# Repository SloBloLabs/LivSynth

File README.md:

# Youtube

Watch the related [Demo Video] on Youtube for a workout in musical context.

Watch the corresponding [Video Manual] on Youtube for a detailed feature explanation.

[Demo Video]: https://youtu.be/7tzhh7atj4o
[Video Manual]: https://youtu.be/lYTFUqn5oQk

# Build Instructions

How to convert a CubeMX / CubeIDE project to GNU ARM Toolchain with CMake, openocd and VS Code

Prerequisites

Available on PATH
 - ARM toolchain
 - make
 - cmake
 - openocd

VS Code extensions
 - MS C/C++
 - MS C/C++ Extension Pack
 - Cortex Debug

---

Workflow

Copy to project directory:
 - README.md
 - Makefile
 - CMakeLists.txt
 - cmake folder with arm toolchain cmake directives
 - .gitignore file
 - swvtrace.sh
 - svd file (optional)
 - folder .vscode/launch.json and adapt settings
 - folder "App"

then
 - Adapt settings in CMakeLists.txt header
 - rename myAppMain [.hpp/.cpp]
 - include myAppMain.hpp in Core/Src/main.c
 - add projectMain() to main.c (right before while loop)
 - right click CMakeLists.txt -> configure all projects
 - start coding

Tested on
 - Mac
 - Linux

2022-03-08: There is an issue using ARM Toolchain 11.2.1: https://community.arm.com/support-forums/f/compilers-and-libraries-forum/52377/internal-compiler-errors-with-arm-none-eabi-gcc-11-2-2022-02-on-macs-with-apple-silicon
Stick with 10.3 for now!!
2022-11-13: The issue is solved within Toolchain version 11.3.1

---

Upload to github
 - git init
 - git add .
 - git config user.name "<<username>>"
 - git config user.email "<<email>>"
 - git commit -m "First commit"
 - git branch -M main
 - git remote add origin https://github.com/SloBloLabs/<"ProjectRepo">.git
 - git push -u origin main

--

Update github access token
 - git remote remove origin
 - git remote add origin https://oauth2:<<new oauth token>>@github.com/<<username>>/<<reponame>>.git
 - git remote -v

--

Bake a new release on Github:
git tag <tagname> // e.g. v0.2.1
git push origin <tagname>

--
# STM32 USB Composite device

Composite USB interface:

1 configuration
3 interfaces (2*CDC + 1*MIDI)
6 endpoints

CDC:
 - 2 interfaces
   - 0: communications control
     - 1 endpoint 0x82
   - 1: communications data
     - 2 endpoints 0x01 + 0x81 (BULK)
 - 4 endpoints overall
   - EP0
   - EP1
   - EP3 (in only: 0x83)

MIDI:
 - 1 interface
   - 0: Audio/Streaming
     - 2 endpoints 0x02 + 0x83 (BULK)
 - 3 endpoints overall
   - EP0
   - EP2

# Build Instructions

Use the ibom tool inside the hardware section of the repository to track your work!
## Power
 - Place USB Micro Connector J21
 - Place all components from power section
   - U8
   - D12
   - FB1
   - U1
   - J24, J24, J12, J7
   - C49, C52, C32, C33, C1, C2, C3, C7
   - R1, R2, R11
   - SW7
 - Check voltages at J201, do proceed if everything is ok!

## Assembly of backside
 - assemble all components (except 5mm LEDs!) on the backside of the mainboard, preferably using the following order:
   - SMD components
   - resistors
   - diodes
   - DIP socket and DIP components
   - transistors (Q4/Q5, Q8/Q9 and Q11/Q12 must be matched)
   - tempco resistor
   - pin headers
   - capacitors

## Assemply of frontside
 - assemble potentiometers, trimmers, spacers and switches of the mainboard, DO NOT SOLDER THEM YET!
 - put the faceplate on top and make sure all components incl. trimmers fit into the wholes
 - fasten the M2.5 screws in the corners
 - turn the set around and solder everthing
 - remove the faceplate again

## Assmebly of speaker
 - First put screws from backside, hex nuts on the front side and tighten them
 - solder the hex nuts to the solder pads
 - apply two pieces of bell wire of about 5cm in lenght to the speakers solder pads
 - remove screws and mount the speaker to the frontside using the screws the other way around
 - if using the battery holder you may need to shorten one of the screws to make it fit
 - connect the loose ends of speaker wires to J4

## LEDs
 - assemble the 5mm LEDs on the backside
 - bend their heads in a 180° U-turn into the holes behind the transparent potentiometers, so they can emit as much light as possible into their shafts

## Flashing the firmware
 - make sure, dfu-util (https://dfu-util.sourceforge.net) is installed on your machine
   - alternatively, you can use stm32 cube programmer (https://www.st.com/en/development-tools/stm32cubeprog.html). I will not further explain this way, but it is a little more user friendly and pretty straight forward.
 - switch off the synthesizer
 - pull the run/program toggle switch next to the micro USB port to lower (program) position
 - connect a USB cable between the synth and your computer
 - switch on the synth again
 - execute the following command:
```
dfu-util -a 0 -s 0x08000000 -D <path to LivSynth.bin>
```
 - The output in the console shoud look similar to this:
```
dfu-util -a 0 -s 0x08000000 -D build/LivSynth.bin
dfu-util 0.11

Copyright 2005-2009 Weston Schmidt, Harald Welte and OpenMoko Inc.
Copyright 2010-2021 Tormod Volden and Stefan Schmidt
This program is Free Software and has ABSOLUTELY NO WARRANTY
Please report bugs to http://sourceforge.net/p/dfu-util/tickets/

dfu-util: Warning: Invalid DFU suffix signature
dfu-util: A valid DFU suffix will be required in a future dfu-util release
Opening DFU capable USB device...
Device ID 0483:df11
Device DFU version 011a
Claiming USB DFU Interface...
Setting Alternate Interface #0 ...
Determining device status...
DFU state(10) = dfuERROR, status(10) = Device's firmware is corrupt. It cannot return to run-time (non-DFU) operations
Clearing status
Determining device status...
DFU state(2) = dfuIDLE, status(0) = No error condition is present
DFU mode device DFU version 011a
Device returned transfer size 2048
DfuSe interface name: "Internal Flash  "
Downloading element to address = 0x08000000, size = 49412
Erase           [=========================] 100%        49412 bytes
Erase    done.
Download        [=========================] 100%        49412 bytes
Download done.
File downloaded successfully
```
 > Hint: if you are building the firmware from the repo, the DFU command is called by simply writing
```
make dfu
```
 - switch off the synth and remove the USB cable
 - pull the run/program switch up (run) again
 - switch on the synth
 - Click <kbd>shift</kbd> + <kbd>run</kbd> to enter sequence control mode
 - press and hold button <kbd>8</kbd> for more than 2 seconds. This will initialize the sequencer program in flash. The synth is now reset.
 - Press <kbd>run</kbd> again to get back to pattern mode

## Test & Calibration
 - connect a 9V center negative power supply to the barrel jack
 - switch on the device and wait a moment. Turn it off again if you see anything suspicious. ("smoke test")
 - At least the keyboard LEDs should light up in white colour and the LFO LEDs are blinking
### VCO
  - SAW amplitude
  - SQUARE amplitude
  - fine tune & tracking
    - Press a button and tune it to the lowest note (red) using the tune knob
    - Press another button and tune it to the red note two octaves higher
    - Press a third button and tune it to the highest red note
### VCA
  - balance...

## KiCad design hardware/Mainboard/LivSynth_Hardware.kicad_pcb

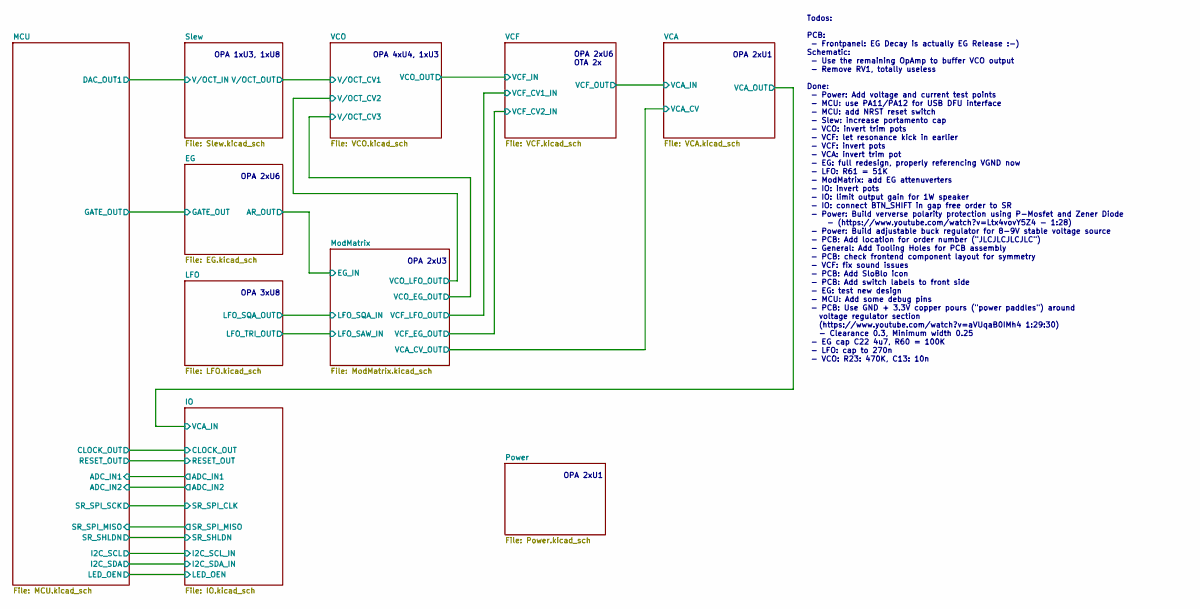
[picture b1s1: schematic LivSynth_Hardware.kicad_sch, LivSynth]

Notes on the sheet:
OPA 1xU3, 1xU8
OPA 2xU6
OPA 3xU8
OPA 2xU3
Todos: PCB: - Frontpanel: EG Decay is actually EG Release :-) Schematic: - Use the remaining OpAmp to buffer VCO output - Remove RV1, totally useless Done: - Power: Add voltage and current test points - MCU: use PA11/PA12 for USB DFU interface - MCU: add NRST reset switch - Slew: increase portament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
OPA 2xU6 OTA 2x
OPA 2xU1
OPA 4xU4, 1xU3

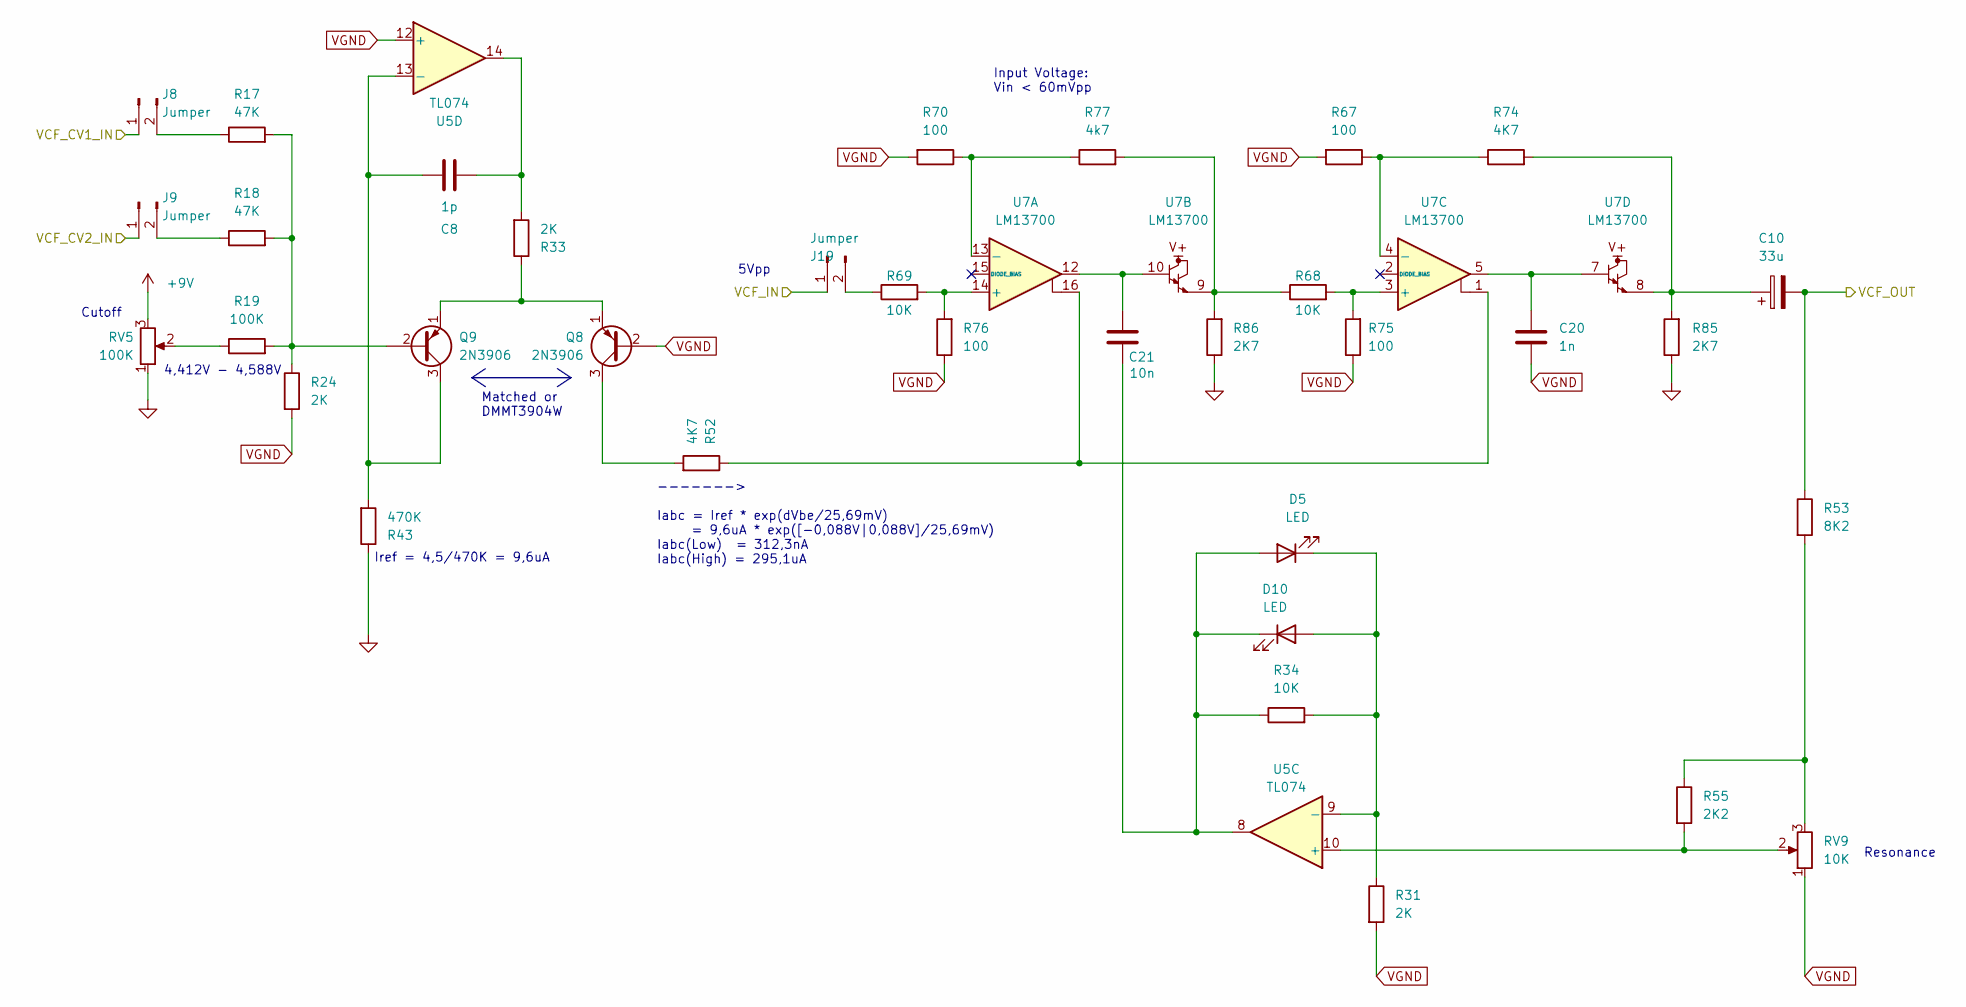
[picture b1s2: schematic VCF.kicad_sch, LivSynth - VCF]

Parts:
C8: 1p; C_Disc_D3.0mm_W1.6mm_P2.50mm
C10: 33u; CP_Radial_D8.0mm_P3.50mm
C20: 1n; C_Rect_L7.2mm_W2.5mm_P5.00mm_FKS2_FKP2_MKS2_MKP2
C21: 10n; C_Rect_L7.2mm_W2.5mm_P5.00mm_FKS2_FKP2_MKS2_MKP2
D5, D10: LED; LED_D5.0mm
J8, J9, J19: Jumper; PinHeader_1x02_P2.54mm_Vertical
Q8, Q9: 2N3906; TO-92_Inline
R17, R18: 47K; R_Axial_DIN0207_L6.3mm_D2.5mm_P7.62mm_Horizontal
R19: 100K; R_Axial_DIN0207_L6.3mm_D2.5mm_P7.62mm_Horizontal
R24, R31, R33: 2K; R_Axial_DIN0207_L6.3mm_D2.5mm_P7.62mm_Horizontal
R34, R68, R69: 10K; R_Axial_DIN0207_L6.3mm_D2.5mm_P7.62mm_Horizontal
R43: 470K; R_Axial_DIN0207_L6.3mm_D2.5mm_P7.62mm_Horizontal
R52, R74: 4K7; R_Axial_DIN0207_L6.3mm_D2.5mm_P7.62mm_Horizontal
R53: 8K2; R_Axial_DIN0207_L6.3mm_D2.5mm_P7.62mm_Horizontal
R55: 2K2; R_Axial_DIN0207_L6.3mm_D2.5mm_P7.62mm_Horizontal
R67, R70, R75, R76: 100; R_Axial_DIN0207_L6.3mm_D2.5mm_P7.62mm_Horizontal
R77: 4k7; R_Axial_DIN0207_L6.3mm_D2.5mm_P7.62mm_Horizontal
R85, R86: 2K7; R_Axial_DIN0207_L6.3mm_D2.5mm_P7.62mm_Horizontal
RV5: 100K; RV141F-40-20BL
RV9: 10K; RV141F-40-20BL
U5: TL074; SOIC-14_3.9x8.7mm_P1.27mm; LCSC C2057504
U7: LM13700; SOP-16_3.9x9.9mm_P1.27mm; LCSC C4370932

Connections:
+9V: RV5.3; also elsewhere on the board
/ModMatrix/VCF_EG_OUT: J9.1; also elsewhere on the board
/ModMatrix/VCF_LFO_OUT: J8.1; also elsewhere on the board
/VCA/VCA_IN: C10.2, R53.1; also elsewhere on the board
/VCF/VCF_IN: J19.1; also elsewhere on the board
GND: R43.1, R85.1, R86.1, RV5.1; also elsewhere on the board
unnamed: C8.2, R33.2, U5.14
unnamed: C10.1, R74.2, R85.2, U7.8
unnamed: C20.1, U7.5, U7.7
unnamed: C21.1, U7.10, U7.12
unnamed: D5.1 (K), D10.2 (A), R31.1, R34.2, U5.9 (-)
unnamed: C21.2, D5.2 (A), D10.1 (K), R34.1, U5.8
unnamed: J8.2, R17.1
unnamed: J9.2, R18.1
unnamed: J19.2, R69.1
unnamed: Q8.3 (C), R52.2
unnamed: Q8.1 (E), Q9.1 (E), R33.1
unnamed: Q9.2 (B), R17.2, R18.2, R19.2, R24.1
unnamed: C8.1, Q9.3 (C), R43.2, U5.13 (-)
unnamed: R19.1, RV5.2
unnamed: R52.1, U7.1, U7.16
unnamed: R53.2, R55.1, RV9.3
unnamed: R68.1, R77.2, R86.2, U7.9
unnamed: R55.2, RV9.2, U5.10 (+)
unnamed: R69.2, R76.2, U7.14 (+)
unnamed: R70.1, R77.1, U7.13 (-)
unnamed: R68.2, R75.2, U7.3 (+)
unnamed: R67.1, R74.1, U7.4 (-)
VGND: C20.2, Q8.2 (B), R24.2, R31.2, R67.2, R70.2, R75.1, R76.1, RV9.1, U5.12 (+); also elsewhere on the board

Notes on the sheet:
Iref = 4,5/470K = 9,6uA
5Vpp
4,412V - 4,588V
-------> Iabc = Iref * exp(dVbe/25,69mV) = 9,6uA * exp([-0,088V|0,088V]/25,69mV) Iabc(Low) = 312,3nA Iabc(High) = 295,1uA
Input Voltage: Vin < 60mVpp
Resonance
Cutoff
Matched or DMMT3904W

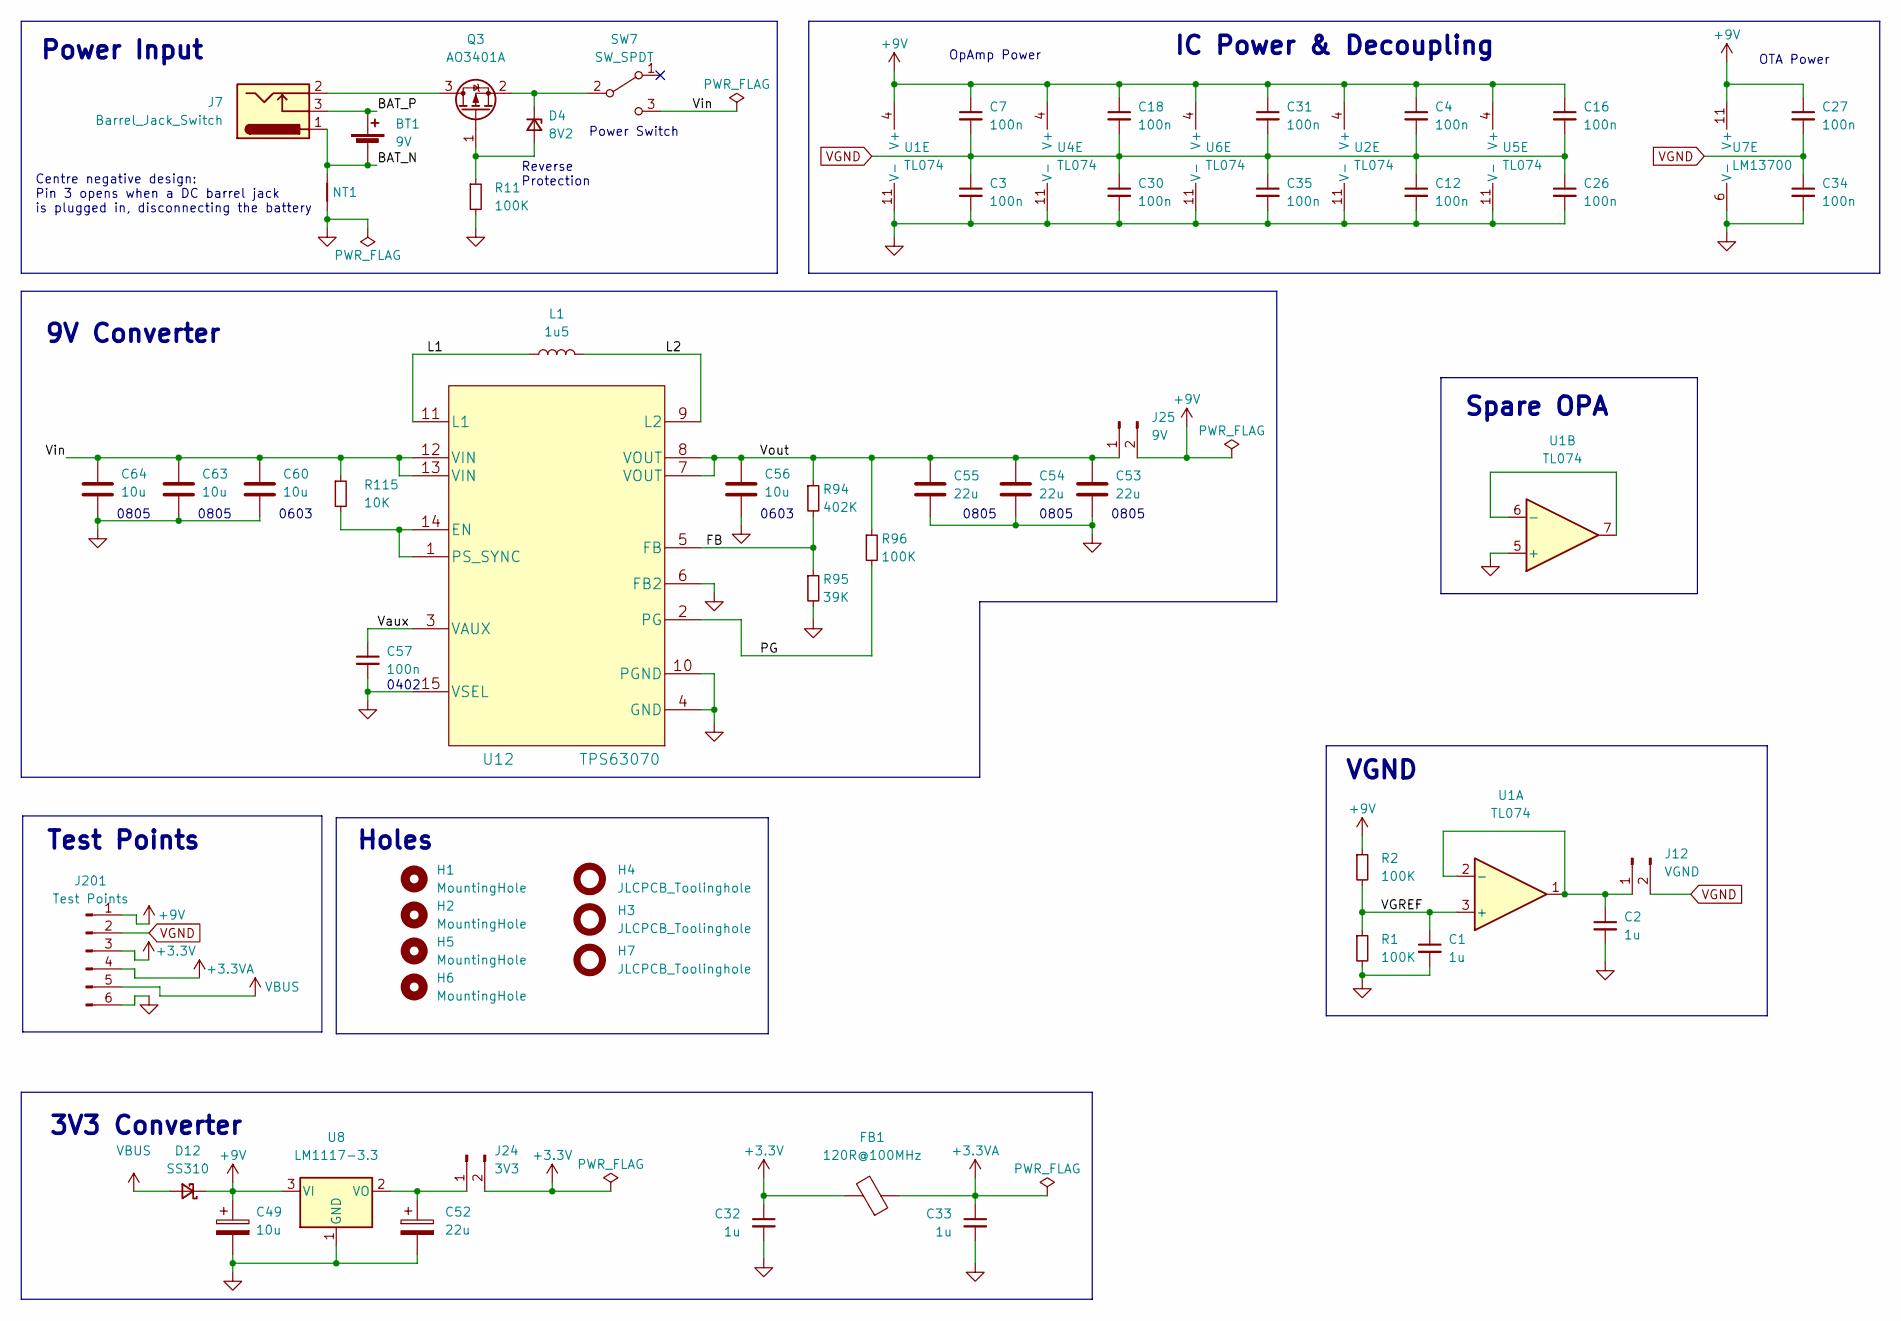
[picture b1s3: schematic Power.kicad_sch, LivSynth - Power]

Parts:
BT1: 9V; BatteryHolder_Eagle_12BH611-GR
C1, C2, C32, C33: 1u; C_Rect_L7.2mm_W5.5mm_P5.00mm_FKS2_FKP2_MKS2_MKP2
C3, C4, C7, C12, C16, C18, C26, C27, C30, C31, C34, C35: 100n; C_Rect_L7.2mm_W2.5mm_P5.00mm_FKS2_FKP2_MKS2_MKP2
C49: 10u; CP_Radial_D8.0mm_P3.50mm
C52: 22u; CP_Radial_D8.0mm_P3.50mm
C53, C54, C55: 22u; C_0805_2012Metric_Pad1.18x1.45mm_HandSolder; LCSC C415296
C56, C60: 10u; C_0603_1608Metric_Pad1.08x0.95mm_HandSolder; LCSC C96446
C57: 100n; C_0402_1005Metric_Pad0.74x0.62mm_HandSolder; LCSC C1523
C63, C64: 10u; C_0805_2012Metric_Pad1.18x1.45mm_HandSolder; LCSC C109040
D4: 8V2; D_SOD-123; LCSC C438308
D12: SS310; D_SMC_Handsoldering
FB1: 120R@100MHz; L_0603_1608Metric
H1, H2, H5, H6: MountingHole; MountingHole_3.2mm_M3
H3, H4, H7: JLCPCB_Toolinghole; JLCPCB_ToolingHole
J7: Barrel_Jack_Switch; BarrelJack_CUI_PJ-102AH_Horizontal
J12: VGND; PinHeader_1x02_P2.54mm_Vertical
J24: 3V3; PinHeader_1x02_P2.54mm_Vertical
J25: 9V; PinHeader_1x02_P2.54mm_Vertical
J201: Test Points; PinHeader_1x06_P2.54mm_Vertical
L1: 1u5; L_Sunlord_SWPA5020S; LCSC C279945
NT1: NetTie_2; NetTie-2_SMD_Pad0.5mm
Q3: AO3401A; SOT-23; LCSC C347476
R1, R2, R11: 100K; R_Axial_DIN0207_L6.3mm_D2.5mm_P7.62mm_Horizontal
R94: 402K; R_0603_1608Metric_Pad0.98x0.95mm_HandSolder; LCSC C844562
R95: 39K; R_0603_1608Metric_Pad0.98x0.95mm_HandSolder; LCSC C163424
R96: 100K; R_0603_1608Metric_Pad0.98x0.95mm_HandSolder; LCSC C25803
R115: 10K; R_0603_1608Metric_Pad0.98x0.95mm_HandSolder; LCSC C25804
SW7: SW_SPDT; SW_E-Switch_EG1224_SPDT_Angled
U1, U2, U4, U5, U6: TL074; SOIC-14_3.9x8.7mm_P1.27mm; LCSC C2057504
U7: LM13700; SOP-16_3.9x9.9mm_P1.27mm; LCSC C4370932
U8: LM1117-3.3; SOT-223-3_TabPin2; LCSC C126027
U12: TPS63070; TPS63070x; LCSC C109322

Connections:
+3.3V: C32.1, FB1.2, J24.2, J201.3; also elsewhere on the board
+3.3VA: C33.1, FB1.1, J201.4; also elsewhere on the board
+9V: C4.1, C7.1, C16.1, C18.1, C27.1, C31.1, C49.1, D12.1 (K), J25.2, J201.1, R2.1, U1.4 (V+), U2.4 (V+), U4.4 (V+), U5.4 (V+), U6.4 (V+), U7.11 (V+), U8.3 (VI); also elsewhere on the board
/ModMatrix/VCF_EG_OUT: U4.1; also elsewhere on the board
/ModMatrix/VCO_EG_OUT: U4.7; also elsewhere on the board
/Power/BAT_N: BT1.2 (-), J7.1, NT1.2
/Power/BAT_P: BT1.1 (+), J7.3
/Power/FB: R94.2, R95.1, U12.5 (FB)
/Power/L1: L1.1, U12.11 (L1)
/Power/L2: L1.2, U12.9 (L2)
/Power/PG: R96.2, U12.2 (PG)
/Power/VGREF: C1.1, R1.1, R2.2, U1.3 (+)
/Power/Vaux: C57.1, U12.3 (VAUX)
/Power/Vin: C60.1, C63.1, C64.1, R115.1, SW7.3 (C), U12.12 (VIN), U12.13 (VIN)
/Power/Vout: C53.1, C54.1, C55.1, C56.1, J25.1, R94.1, R96.1, U12.7 (VOUT), U12.8 (VOUT)
/Slew/V/OCT_OUT: U4.8, U4.9 (-); also elsewhere on the board
GND: C1.2, C2.2, C3.2, C12.2, C26.2, C30.2, C32.2, C33.2, C34.2, C35.2, C49.2, C52.2, C53.2, C54.2, C55.2, C56.2, C57.2, C60.2, C63.2, C64.2, J201.6, NT1.1, R1.2, R11.2, R95.2, U1.5 (+), U1.11 (V-), U2.11 (V-), U4.11 (V-), U5.11 (V-), U6.11 (V-), U7.6 (V-), U8.1 (GND), U12.4 (GND), U12.6 (FB2), U12.10 (PGND), U12.15 (VSEL); also elsewhere on the board
unnamed: D4.2 (A), Q3.1 (G), R11.1
unnamed: D4.1 (K), Q3.2 (S), SW7.2 (B)
unnamed: C2.1, J12.1, U1.1, U1.2 (-)
unnamed: C52.1, J24.1, U8.2 (VO)
unnamed: J7.2, Q3.3 (D)
unnamed 179: U1.14; also elsewhere on the board
unnamed 180: U1.8; also elsewhere on the board
unnamed 191: U6.8; also elsewhere on the board
unnamed: U1.6 (-), U1.7
unnamed 226: U1.9 (-); also elsewhere on the board
unnamed 227: U1.12 (+); also elsewhere on the board
unnamed 228: U1.13 (-); also elsewhere on the board
unnamed 235: U4.3 (+); also elsewhere on the board
unnamed 236: U4.2 (-); also elsewhere on the board
unnamed 237: U4.5 (+); also elsewhere on the board
unnamed 238: U4.6 (-); also elsewhere on the board
unnamed 239: U4.10 (+); also elsewhere on the board
unnamed 245: U6.10 (+); also elsewhere on the board
unnamed 246: U6.9 (-); also elsewhere on the board
unnamed: R115.2, U12.1 (PS_SYNC), U12.14 (EN)
VBUS: D12.2 (A), J201.5; also elsewhere on the board
VGND: C3.1, C4.2, C7.2, C12.1, C16.2, C18.2, C26.1, C27.2, C30.1, C31.2, C34.1, C35.1, J12.2, J201.2, U1.10 (+); also elsewhere on the board

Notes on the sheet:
9V Converter
0603
Centre negative design: Pin 3 opens when a DC barrel jack is plugged in, disconnecting the battery
0402
0805
Test Points
3V3 Converter
OTA Power
Power Switch
OpAmp Power
VGND
Spare OPA
IC Power & Decoupling
Reverse Protection
Holes
Power Input

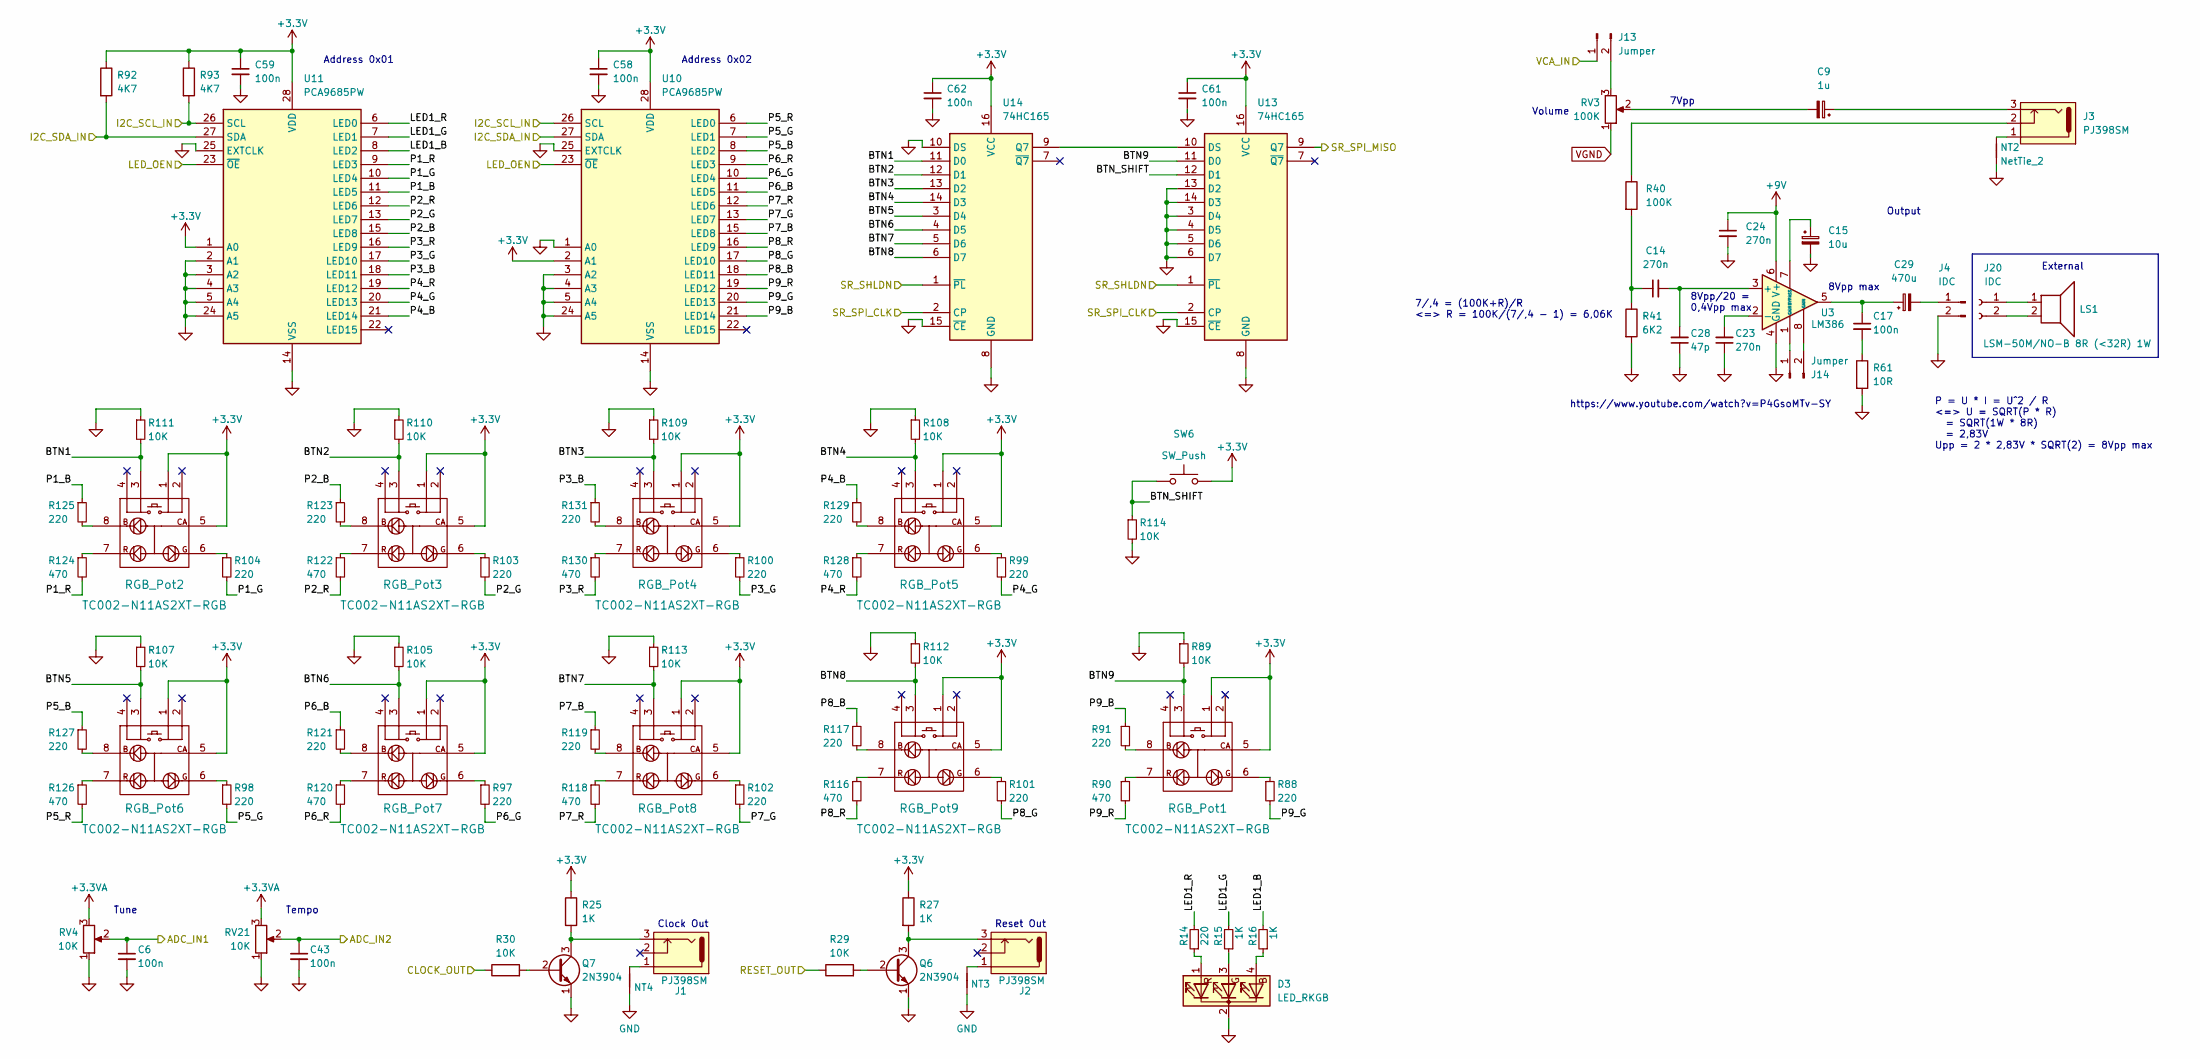
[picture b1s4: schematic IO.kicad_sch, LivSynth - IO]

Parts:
C6, C17, C43, C58, C59, C61, C62: 100n; C_Rect_L7.2mm_W2.5mm_P5.00mm_FKS2_FKP2_MKS2_MKP2
C9: 1u; C_Rect_L7.2mm_W5.5mm_P5.00mm_FKS2_FKP2_MKS2_MKP2
C14, C23, C24: 270n; C_Rect_L7.2mm_W4.5mm_P5.00mm_FKS2_FKP2_MKS2_MKP2
C15: 10u; CP_Radial_D8.0mm_P3.50mm
C28: 47p; C_Disc_D3.0mm_W1.6mm_P2.50mm
C29: 470u; CP_Radial_D8.0mm_P3.50mm
D3: LED_RKGB; LED_D5.0mm-4_RGB
J1, J2, J3: PJ398SM; Thonkiconn_PJ398SM
J4: IDC; PinHeader_1x02_P2.54mm_Vertical
J13, J14: Jumper; PinHeader_1x02_P2.54mm_Vertical
J20: IDC
LS1: LSM-50M/NO-B 8R (<32R) 1W; LSM-50M NO-B
NT2, NT3, NT4: NetTie_2; NetTie-2_SMD_Pad0.5mm
Q6, Q7: 2N3904; TO-92_Inline
R14, R88, R91, R97, R98, R99, R100, R101, R102, R103, R104, R117, R119, R121, R123, R125, R127, R129, R131: 220; R_Axial_DIN0207_L6.3mm_D2.5mm_P7.62mm_Horizontal
R15, R16, R25, R27: 1K; R_Axial_DIN0207_L6.3mm_D2.5mm_P7.62mm_Horizontal
R29, R30, R89, R105, R107, R108, R109, R110, R111, R112, R113, R114: 10K; R_Axial_DIN0207_L6.3mm_D2.5mm_P7.62mm_Horizontal
R40: 100K; R_Axial_DIN0207_L6.3mm_D2.5mm_P7.62mm_Horizontal
R41: 6K2; R_Axial_DIN0207_L6.3mm_D2.5mm_P7.62mm_Horizontal
R61: 10R; R_Axial_DIN0207_L6.3mm_D2.5mm_P7.62mm_Horizontal
R90, R116, R118, R120, R122, R124, R126, R128, R130: 470; R_Axial_DIN0207_L6.3mm_D2.5mm_P7.62mm_Horizontal
R92, R93: 4K7; R_Axial_DIN0207_L6.3mm_D2.5mm_P7.62mm_Horizontal
RGB_Pot1, RGB_Pot2, RGB_Pot3, RGB_Pot4, RGB_Pot5, RGB_Pot6, RGB_Pot7, RGB_Pot8, RGB_Pot9: TC002-N11AS2XT-RGB
RV3: 100K; Alpha_RD901F
RV4: 10K; RV141F-40-20BL
RV21: 10K; Alpha_RD901F
SW6: SW_Push; E-Switch_TL1105SP
U3: LM386; DIP-8_W7.62mm_Socket
U10, U11: PCA9685PW; TSSOP-28_4.4x9.7mm_P0.65mm; LCSC C2678753
U13, U14: 74HC165; SOIC-16_3.9x9.9mm_P1.27mm; LCSC C7334

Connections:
+3.3V: C58.1, C59.1, C61.1, C62.1, R25.1, R27.1, R92.1, R93.1, RGB_Pot1.1 (UP-A), RGB_Pot1.5 (CA), RGB_Pot2.1 (UP-A), RGB_Pot2.5 (CA), RGB_Pot3.1 (UP-A), RGB_Pot3.5 (CA), RGB_Pot4.1 (UP-A), RGB_Pot4.5 (CA), RGB_Pot5.1 (UP-A), RGB_Pot5.5 (CA), RGB_Pot6.1 (UP-A), RGB_Pot6.5 (CA), RGB_Pot7.1 (UP-A), RGB_Pot7.5 (CA), RGB_Pot8.1 (UP-A), RGB_Pot8.5 (CA), RGB_Pot9.1 (UP-A), RGB_Pot9.5 (CA), SW6.2, U10.2 (A1), U10.28 (VDD), U11.1 (A0), U11.28 (VDD), U13.16 (VCC), U14.16 (VCC); also elsewhere on the board
+3.3VA: RV4.3, RV21.3; also elsewhere on the board
+9V: C24.1, U3.6 (V+); also elsewhere on the board
/IO/ADC_IN1: C6.1, RV4.2; also elsewhere on the board
/IO/ADC_IN2: C43.1, RV21.2; also elsewhere on the board
/IO/BTN1: R111.2, RGB_Pot2.3 (DOWN-A), U14.11 (D0)
/IO/BTN2: R110.2, RGB_Pot3.3 (DOWN-A), U14.12 (D1)
/IO/BTN3: R109.2, RGB_Pot4.3 (DOWN-A), U14.13 (D2)
/IO/BTN4: R108.2, RGB_Pot5.3 (DOWN-A), U14.14 (D3)
/IO/BTN5: R107.2, RGB_Pot6.3 (DOWN-A), U14.3 (D4)
/IO/BTN6: R105.2, RGB_Pot7.3 (DOWN-A), U14.4 (D5)
/IO/BTN7: R113.2, RGB_Pot8.3 (DOWN-A), U14.5 (D6)
/IO/BTN8: R112.2, RGB_Pot9.3 (DOWN-A), U14.6 (D7)
/IO/BTN9: R89.2, RGB_Pot1.3 (DOWN-A), U13.11 (D0); also elsewhere on the board
/IO/BTN_SHIFT: R114.1, SW6.1, U13.12 (D1); also elsewhere on the board
/IO/CLOCK_OUT: R30.1; also elsewhere on the board
/IO/I2C_SCL_IN: R93.2, U10.26 (SCL), U11.26 (SCL); also elsewhere on the board
/IO/I2C_SDA_IN: R92.2, U10.27 (SDA), U11.27 (SDA); also elsewhere on the board
/IO/LED1_B: R16.2, U11.8 (LED2)
/IO/LED1_G: R15.2, U11.7 (LED1)
/IO/LED1_R: R14.2, U11.6 (LED0)
/IO/LED_OEN: U10.23 (~OE), U11.23 (~OE); also elsewhere on the board
/IO/P1_B: R125.1, U11.11 (LED5)
/IO/P1_G: R104.2, U11.10 (LED4)
/IO/P1_R: R124.2, U11.9 (LED3)
/IO/P2_B: R123.1, U11.15 (LED8)
/IO/P2_G: R103.2, U11.13 (LED7)
/IO/P2_R: R122.2, U11.12 (LED6)
/IO/P3_B: R131.1, U11.18 (LED11)
/IO/P3_G: R100.2, U11.17 (LED10)
/IO/P3_R: R130.2, U11.16 (LED9)
/IO/P4_B: R129.1, U11.21 (LED14)
/IO/P4_G: R99.2, U11.20 (LED13)
/IO/P4_R: R128.2, U11.19 (LED12)
/IO/P5_B: R127.1, U10.8 (LED2)
/IO/P5_G: R98.2, U10.7 (LED1); also elsewhere on the board
/IO/P5_R: R126.2, U10.6 (LED0)
/IO/P6_B: R121.1, U10.11 (LED5)
/IO/P6_G: R97.2, U10.10 (LED4)
/IO/P6_R: R120.2, U10.9 (LED3)
/IO/P7_B: R119.1, U10.15 (LED8)
/IO/P7_G: R102.2, U10.13 (LED7)
/IO/P7_R: R118.2, U10.12 (LED6)
/IO/P8_B: R117.1, U10.18 (LED11)
/IO/P8_G: R101.2, U10.17 (LED10)
/IO/P8_R: R116.2, U10.16 (LED9)
/IO/P9_B: R91.1, U10.21 (LED14)
/IO/P9_G: R88.2, U10.20 (LED13)
/IO/P9_R: R90.2, U10.19 (LED12)
/IO/RESET_OUT: R29.1; also elsewhere on the board
/IO/SR_SHLDN: U13.1 (~PL), U14.1 (~PL); also elsewhere on the board
/IO/SR_SPI_CLK: U13.2 (CP), U14.2 (CP); also elsewhere on the board
/IO/VCA_IN: J13.1; also elsewhere on the board
GND: C6.2, C15.2, C23.1, C24.2, C28.1, C43.2, C58.2, C59.2, C61.2, C62.2, D3.2 (K), J4.2, NT2.1, NT3.1, NT4.1, Q6.1 (E), Q7.1 (E), R41.2, R61.2, R89.1, R105.1, R107.1, R108.1, R109.1, R110.1, R111.1, R112.1, R113.1, R114.2, RV4.1, RV21.1, U3.4 (GND), U10.1 (A0), U10.3 (A2), U10.4 (A3), U10.5 (A4), U10.14 (VSS), U10.24 (A5), U10.25 (EXTCLK), U11.2 (A1), U11.3 (A2), U11.4 (A3), U11.5 (A4), U11.14 (VSS), U11.24 (A5), U11.25 (EXTCLK), U13.3 (D4), U13.4 (D5), U13.5 (D6), U13.6 (D7), U13.8 (GND), U13.13 (D2), U13.14 (D3), U13.15 (~CE), U14.8 (GND), U14.10 (DS), U14.15 (~CE); also elsewhere on the board
unnamed: C9.1, J3.3
unnamed: C9.2, RV3.2
unnamed: C14.1, R40.2, R41.1
unnamed: C17.1, C29.1, U3.5
unnamed: C17.2, R61.1
unnamed: D3.4 (BA), R16.1
unnamed: D3.3 (GA), R15.1
unnamed: D3.1 (RA), R14.1
unnamed: J1.1, NT4.2
unnamed: J2.1, NT3.2
unnamed: J3.1, NT2.2
unnamed: J3.2, R40.1
unnamed: C29.2, J4.1
unnamed: J13.2, RV3.3
unnamed: J14.1, U3.1 (GAIN)
unnamed: J14.2, U3.8 (GAIN)
unnamed: J20.1, LS1.1
unnamed: J20.2, LS1.2
unnamed: Q6.2 (B), R29.2
unnamed: J2.3, Q6.3 (C), R27.2
unnamed: Q7.2 (B), R30.2
unnamed: J1.3, Q7.3 (C), R25.2
unnamed: R91.2, RGB_Pot1.8 (B)
unnamed: R88.1, RGB_Pot1.6 (G)
unnamed: R90.1, RGB_Pot1.7 (R)
unnamed: R125.2, RGB_Pot2.8 (B)
unnamed: R104.1, RGB_Pot2.6 (G)
unnamed: R124.1, RGB_Pot2.7 (R)
unnamed: R123.2, RGB_Pot3.8 (B)
unnamed: R103.1, RGB_Pot3.6 (G)
unnamed: R122.1, RGB_Pot3.7 (R)
unnamed: R131.2, RGB_Pot4.8 (B)
unnamed: R100.1, RGB_Pot4.6 (G)
unnamed: R130.1, RGB_Pot4.7 (R)
unnamed: R129.2, RGB_Pot5.8 (B)
unnamed: R99.1, RGB_Pot5.6 (G)
unnamed: R128.1, RGB_Pot5.7 (R)
unnamed: R127.2, RGB_Pot6.8 (B)
unnamed 208: R98.1, RGB_Pot6.6 (G); also elsewhere on the board
unnamed: R126.1, RGB_Pot6.7 (R)
unnamed: R121.2, RGB_Pot7.8 (B)
unnamed: R97.1, RGB_Pot7.6 (G)
unnamed: R120.1, RGB_Pot7.7 (R)
unnamed: R119.2, RGB_Pot8.8 (B)
unnamed: R102.1, RGB_Pot8.6 (G)
unnamed: R118.1, RGB_Pot8.7 (R)
unnamed: R117.2, RGB_Pot9.8 (B)
unnamed: R101.1, RGB_Pot9.6 (G)
unnamed: R116.1, RGB_Pot9.7 (R)
unnamed: C14.2, C28.2, U3.3 (+)
unnamed: C23.2, U3.2 (-)
unnamed: C15.1, U3.7 (BYPASS)
unnamed 253: U13.10 (DS), U14.9 (Q7); also elsewhere on the board
VGND: RV3.1; also elsewhere on the board

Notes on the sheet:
Address 0x01
Clock Out
8Vpp/20 = 0,4Vpp max
https://www.youtube.com/watch?v=P4GsoMTv-SY
Tempo
Tune
Output
7/,4 = (100K+R)/R <=> R = 100K/(7/,4 - 1) = 6,06K
Address 0x02
Volume
Reset Out
External
8Vpp max
P = U * I = U^2 / R <=> U = SQRT(P * R) = SQRT(1W * 8R) = 2,83V Upp = 2 * 2,83V * SQRT(2) = 8Vpp max
7Vpp

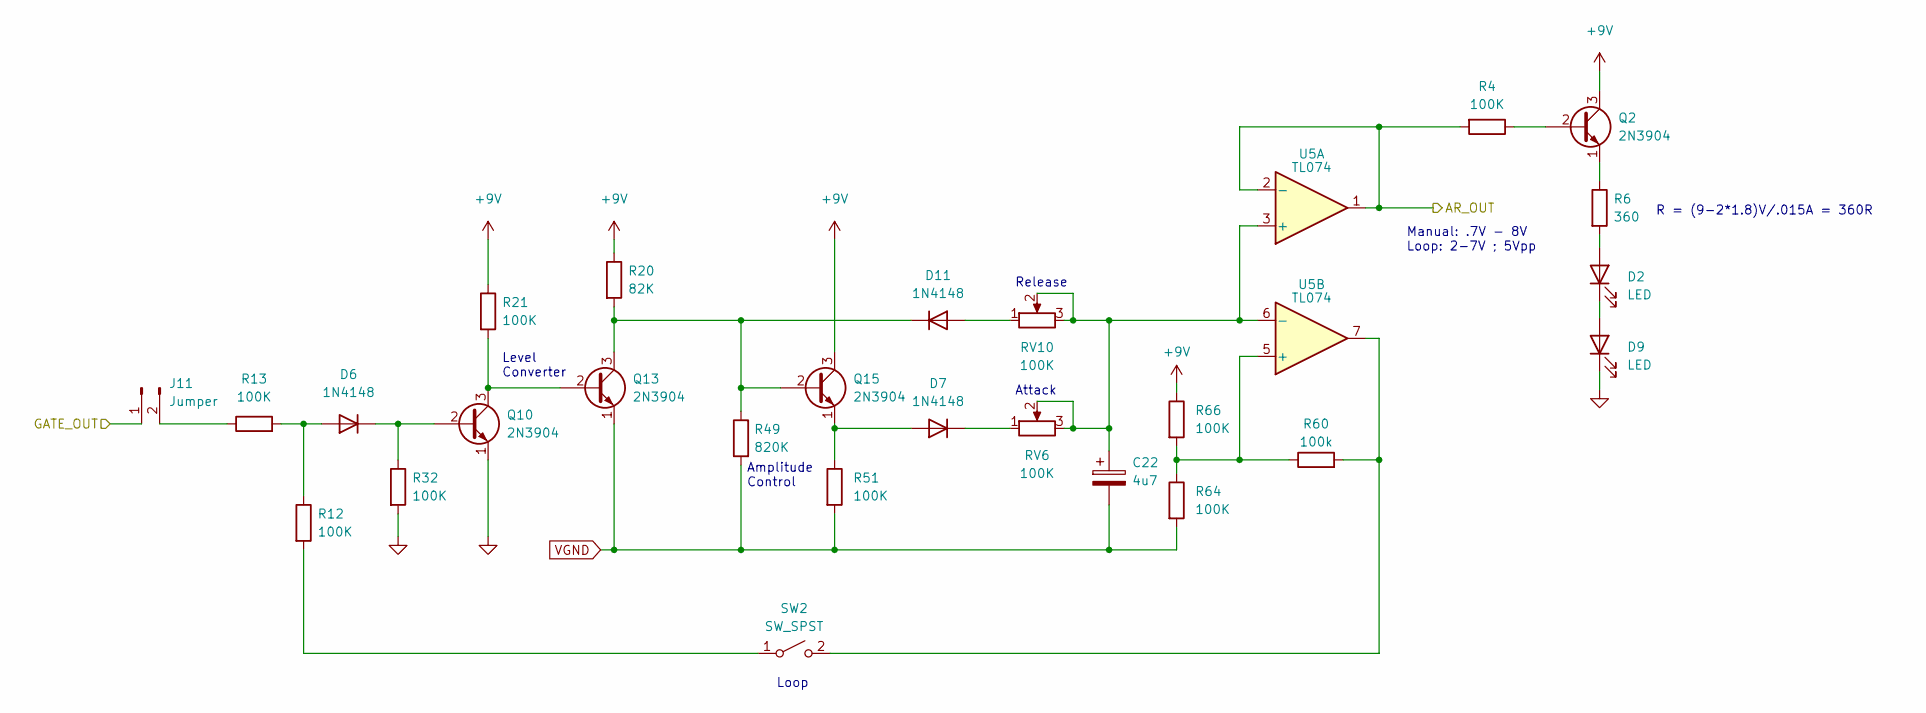
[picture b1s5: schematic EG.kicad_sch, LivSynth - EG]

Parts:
C22: 4u7; CP_Radial_D8.0mm_P3.50mm
D2, D9: LED; LED_D5.0mm
D6, D7, D11: 1N4148; D_DO-35_SOD27_P7.62mm_Horizontal
J11: Jumper; PinHeader_1x02_P2.54mm_Vertical
Q2, Q10, Q13, Q15: 2N3904; TO-92_Inline
R4, R12, R13, R21, R32, R51, R64, R66: 100K; R_Axial_DIN0207_L6.3mm_D2.5mm_P7.62mm_Horizontal
R6: 360; R_Axial_DIN0207_L6.3mm_D2.5mm_P7.62mm_Horizontal
R20: 82K; R_Axial_DIN0207_L6.3mm_D2.5mm_P7.62mm_Horizontal
R49: 820K; R_Axial_DIN0207_L6.3mm_D2.5mm_P7.62mm_Horizontal
R60: 100k; R_Axial_DIN0207_L6.3mm_D2.5mm_P7.62mm_Horizontal
RV6, RV10: 100K; RV141F-40-20BL
SW2: SW_SPST; SW_Toggle_MS500
U5: TL074; SOIC-14_3.9x8.7mm_P1.27mm; LCSC C2057504

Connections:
+9V: Q2.3 (C), Q15.3 (C), R20.1, R21.1, R66.1; also elsewhere on the board
/EG/AR_OUT: R4.2, U5.1, U5.2 (-); also elsewhere on the board
/EG/GATE_OUT: J11.1; also elsewhere on the board
GND: D9.1 (K), Q10.1 (E), R32.2; also elsewhere on the board
unnamed: D2.2 (A), R6.2
unnamed: D2.1 (K), D9.2 (A)
unnamed: D6.2 (A), R12.1, R13.2
unnamed: D6.1 (K), Q10.2 (B), R32.1
unnamed: D7.2 (A), Q15.1 (E), R51.1
unnamed: D7.1 (K), RV6.1
unnamed: D11.2 (A), RV10.1
unnamed: D11.1 (K), Q13.3 (C), Q15.2 (B), R20.2, R49.1
unnamed: J11.2, R13.1
unnamed: Q2.2 (B), R4.1
unnamed: Q2.1 (E), R6.1
unnamed: Q10.3 (C), Q13.2 (B), R21.2
unnamed: R12.2, SW2.1 (A)
unnamed: R60.2, SW2.2 (B), U5.7
unnamed: C22.1, RV6.2, RV6.3, RV10.2, RV10.3, U5.3 (+), U5.6 (-)
unnamed: R60.1, R64.1, R66.2, U5.5 (+)
VGND: C22.2, Q13.1 (E), R49.2, R51.2, R64.2; also elsewhere on the board

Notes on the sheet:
R = (9-2*1.8)V/.015A = 360R
Attack
Amplitude Control
Release
Loop
Level Converter
Manual: .7V - 8V Loop: 2-7V ; 5Vpp
